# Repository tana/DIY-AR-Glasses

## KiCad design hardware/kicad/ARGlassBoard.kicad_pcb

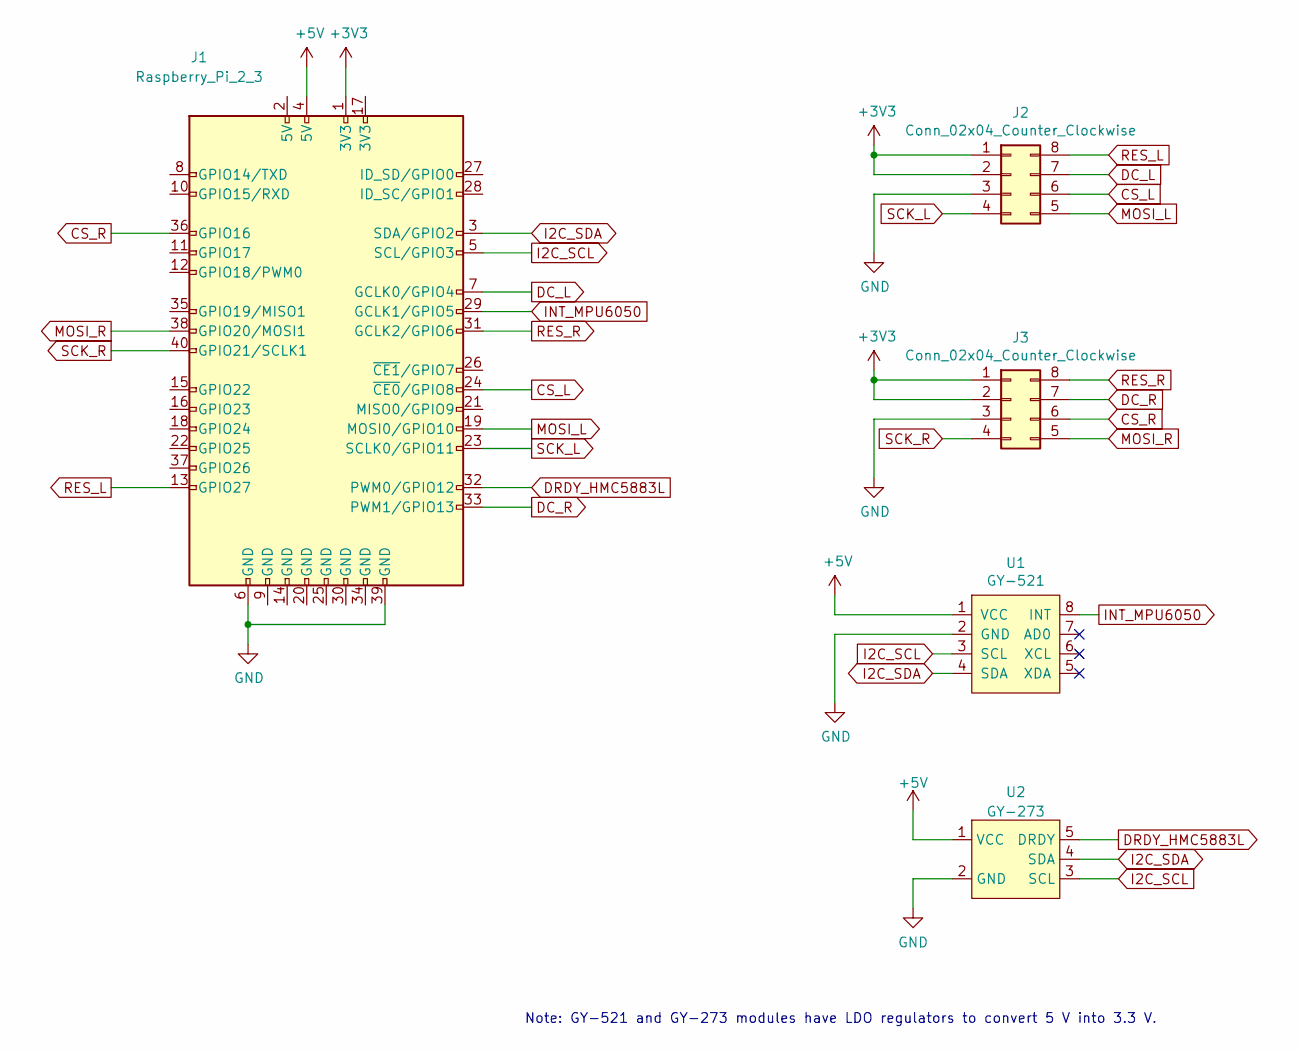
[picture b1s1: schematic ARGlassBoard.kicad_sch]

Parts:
J1: Raspberry_Pi_2_3; PinHeader_2x20_P2.54mm_Vertical
J2, J3: Conn_02x04_Counter_Clockwise; PinHeader_2x04_P2.54mm_Horizontal
U1: GY-521
U2: GY-273

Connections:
+3V3: J1.1 (3V3), J2.1, J2.2, J3.1, J3.2
+5V: J1.4 (5V), U1.1 (VCC), U2.1 (VCC)
CS_L: J1.24 (~CE0/GPIO8), J2.6
CS_R: J1.36 (GPIO16), J3.6
DC_L: J1.7 (GCLK0/GPIO4), J2.7
DC_R: J1.33 (PWM1/GPIO13), J3.7
DRDY_HMC5883L: J1.32 (PWM0/GPIO12), U2.5 (DRDY)
GND: J1.6 (GND), J1.39 (GND), J2.3, J3.3, U1.2 (GND), U2.2 (GND)
I2C_SCL: J1.5 (SCL/GPIO3), U1.3 (SCL), U2.3 (SCL)
I2C_SDA: J1.3 (SDA/GPIO2), U1.4 (SDA), U2.4 (SDA)
INT_MPU6050: J1.29 (GCLK1/GPIO5), U1.8 (INT)
MOSI_L: J1.19 (MOSI0/GPIO10), J2.5
MOSI_R: J1.38 (GPIO20/MOSI1), J3.5
RES_L: J1.13 (GPIO27), J2.8
RES_R: J1.31 (GCLK2/GPIO6), J3.8
SCK_L: J1.23 (SCLK0/GPIO11), J2.4
SCK_R: J1.40 (GPIO21/SCLK1), J3.4

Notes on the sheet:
Note: GY-521 and GY-273 modules have LDO regulators to convert 5 V into 3.3 V.

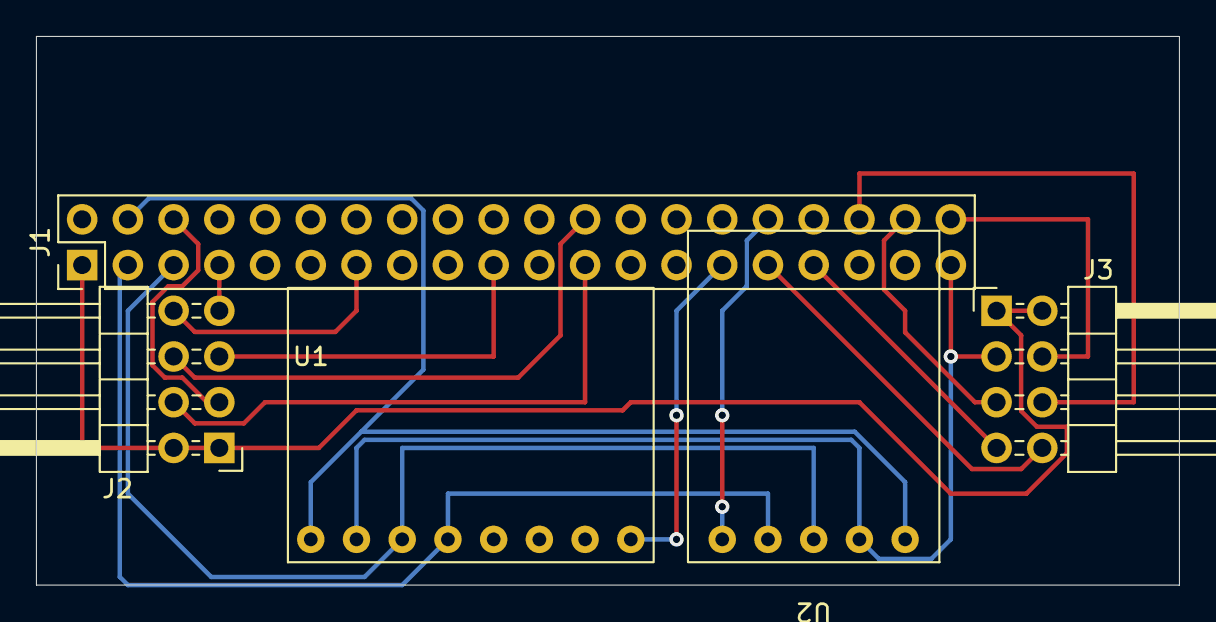
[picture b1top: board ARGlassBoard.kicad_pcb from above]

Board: 2 copper layers, 63.5 x 30.5 mm, 5 parts (0 on the bottom side), 17 nets.

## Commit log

2022-03-06 Add startup script
2022-03-06 Automatic startup using systemd
2022-03-06 Create Raylib program
2022-03-06 Rendering using render textures
2022-03-06 Auto-start the Raylib program
2022-03-07 (WIP) gamepad control
2022-03-08 Change directory structure and update CMakeLists for development on PC
2022-03-08 Add App class and input abstraction layer
2022-03-08 Add menu
2022-03-08 Fix for actual device
2022-03-10 Add app transition system
2022-03-12 Implement distortion correction and adjustment
2022-03-12 Fix shader for OpenGL ES
2022-03-12 Fix fbcp parameter
2022-03-13 Consider shift of displays during distortion compensation
2022-03-13 Draw black background behind text in calibration app to improve visiblity
2022-03-13 Move display size from constant into optical parameter
2022-03-15 Add 3D rendering
2022-03-15 Rename LensParameters into EyeParameters
2022-03-19 Add button control in Test3DApp
2022-03-20 (WIP) implementing IMU driver
2022-03-21 Implement MPU6050 driver
2022-03-21 (WIP) Writing driver for HMC5883L
2022-03-21 Fix bugs in sensor drivers
2022-03-23 Add sensor fusion. Needs debug
2022-03-24 Temporarily ignore magnetometer
2022-03-24 Add magnetometer calibration
2022-03-24 (WIP) Use attitude from sensor in rendering
2022-03-28 Make attitude estimation better but still unstable
2022-03-28 (WIP) Debugging attitude estimation
2022-03-30 Fix attitude estimation
2022-03-31 Fix orientation and some code cleanup
2022-04-03 Add hardware CAD files
2022-04-03 Create LICENSE
2022-07-07 Sensor processing in separate thread
2022-07-07 Fix a bug (sensor processing result was NaN)
